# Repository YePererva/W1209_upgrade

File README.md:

# W1209 modification

**Repository is work in progress**

This repository contains my vision of modification of widely used W1209 thermostat.
Here, I want to introduce following changes:
- add "universal" schematic to use with either:
  - 10-20K NTC (as original W1209)
  - DS18B20
  - TMP36 and alike
  - LMx35 and alike
- add a capacitor for RESET line of to prevent self-restart\
  as reported here: [1](https://sampawno.ru/viewtopic.php?f=120&t=13251)
- Replace some custom sized SRA-12VDC-AL relay with more generiac. Like OMRON or something

# Remarks
- These thermostats were designed with [STM8S103F3P6](https://www.st.com/resource/en/datasheet/stm8s103f2.pdf) microcontrollers, but there are variations with [Nuvoton N76003AT20](https://direct.nuvoton.com/en/n76e003at20) MCU. The spare microcontroller can be salvaged from cheap STM8S103F3P6 devboards \
  (examples [1](https://vivonomicon.com/2018/07/15/the-w1209-a-sometimes-stm8-based-digital-thermostat/), [2](https://www.youtube.com/watch?v=e2FIBK9F2Js)).

# References
- The schematic of original module is "reviewed" here: \
  [1](https://chinese-electronics-products-tested.blogspot.com/p/w1209-temperature-controller-tested.html),
  [2](http://www.mastervintik.ru/obzor-tsifrovogo-modulya-termoregulyatora-w1209/),
  [3](https://tenbaht.github.io/sduino/hardware/w1209-thermostat/)

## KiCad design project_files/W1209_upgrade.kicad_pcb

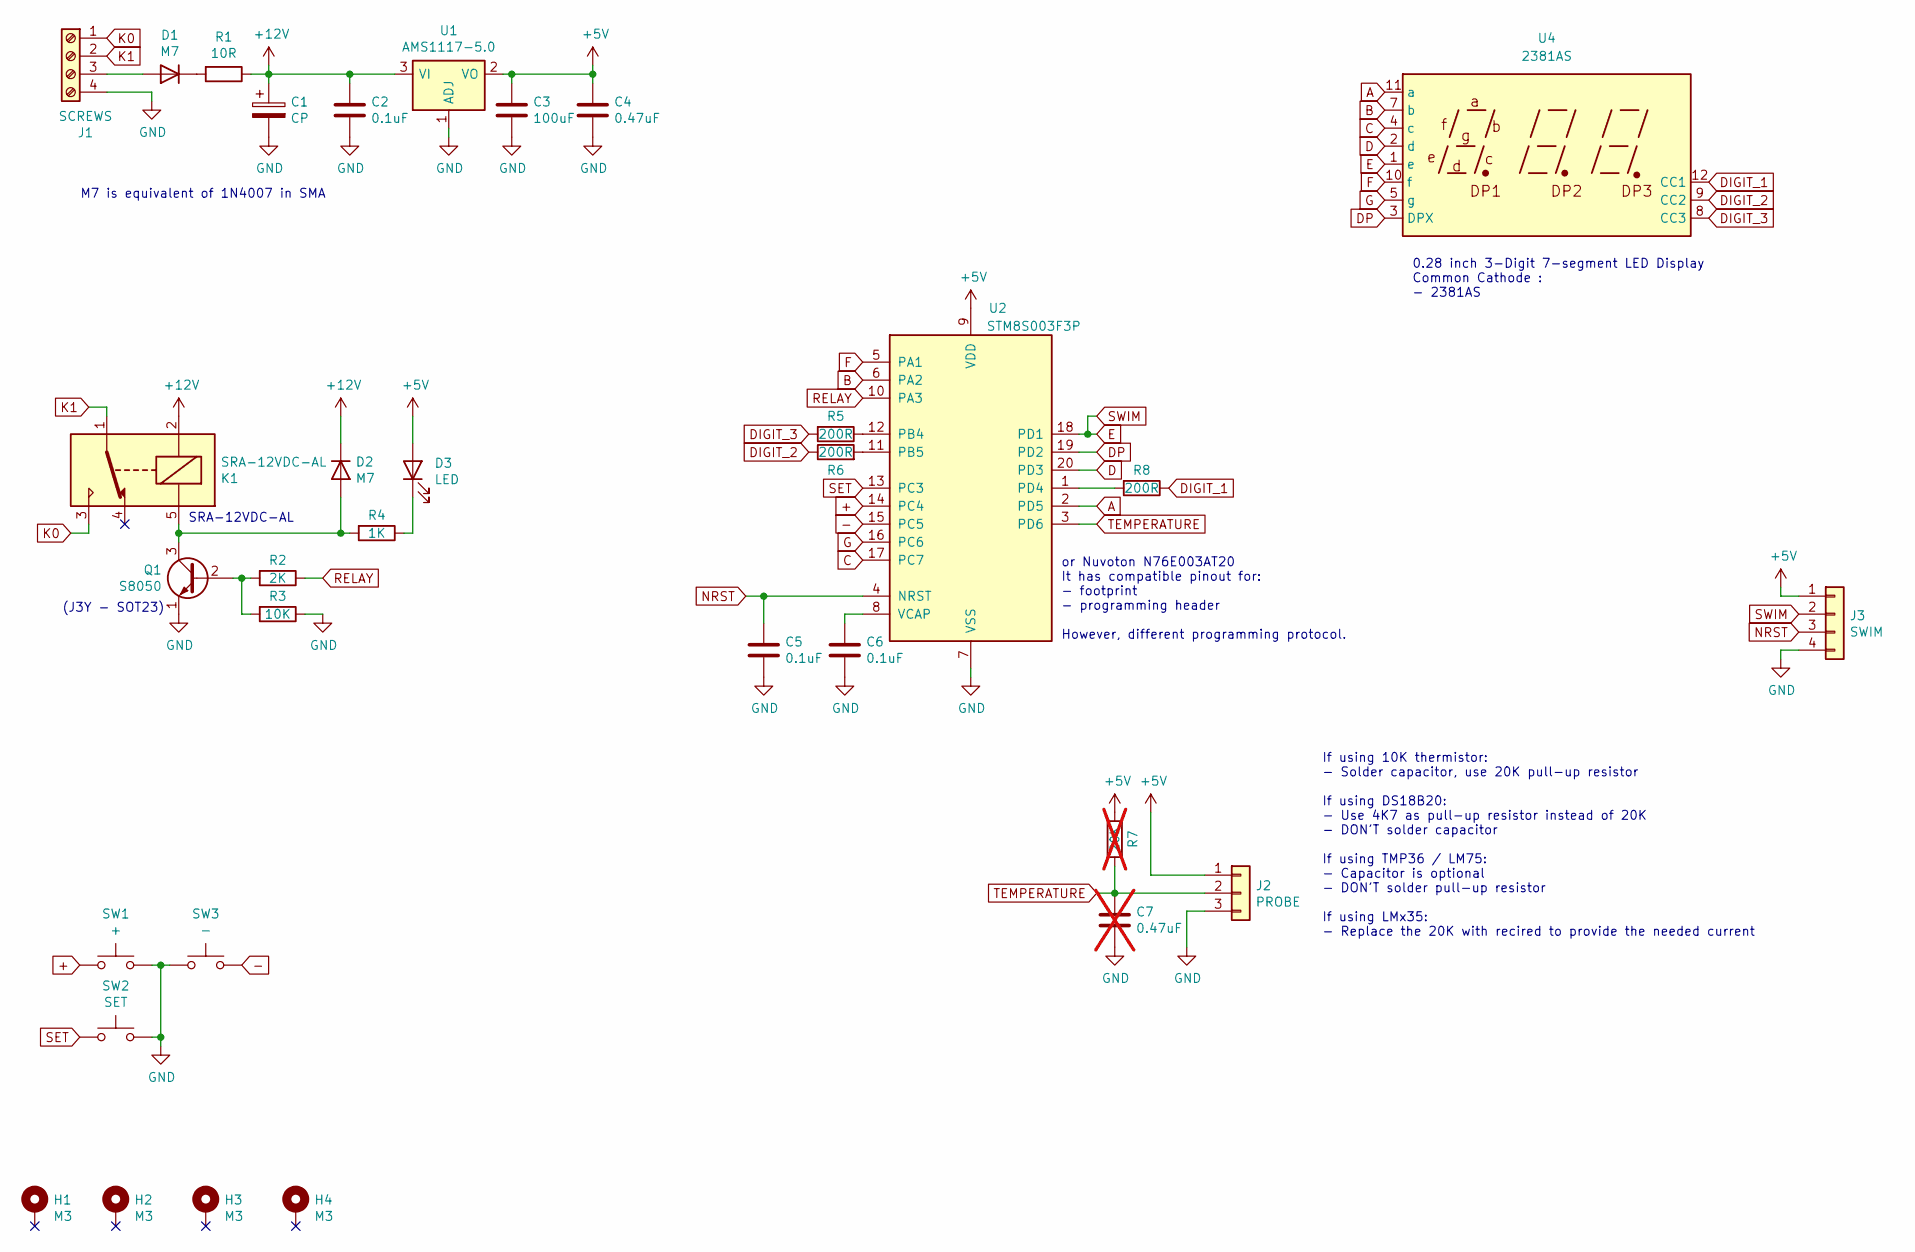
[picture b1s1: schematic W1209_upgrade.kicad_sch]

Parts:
C1: CP; CP_EIA-3528-12_Kemet-T_HandSolder
C2, C5, C6: 0.1uF; C_0805_2012Metric
C3: 100uF; C_0805_2012Metric
C4: 0.47uF; C_0805_2012Metric
C7: 0.47uF; C_0805_2012Metric; not fitted
D1, D2: M7; D_SMA
D3: LED; LED_0805_2012Metric
H1, H2, H3, H4: M3; MountingHole_3.2mm_M3_ISO14580_Pad
J1: SCREWS; TerminalBlock_Phoenix_PT-1,5-4-3.5-H_1x04_P3.50mm_Horizontal
J2: PROBE; PinHeader_1x03_P2.54mm_Vertical
J3: SWIM; PinHeader_1x04_P2.54mm_Vertical
K1: SRA-12VDC-AL; SRA
Q1: S8050; SOT-23
R1: 10R; R_0805_2012Metric
R2: 2K; R_0805_2012Metric
R3: 10K; R_0805_2012Metric
R4: 1K; R_0805_2012Metric
R5, R6, R8: 200R; R_0805_2012Metric
R7: 20K; R_0805_2012Metric; not fitted
SW1: +; SW_PUSH_6mm
SW2: SET; SW_PUSH_6mm
SW3: -; SW_PUSH_6mm
U1: AMS1117-5.0; SOT-223-3_TabPin2
U2: STM8S003F3P; TSSOP-20_4.4x6.5mm_P0.65mm
U4: 2381AS; 2381

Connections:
+: SW1.1, U2.14 (PC4)
+5V: C3.1, C4.1, D3.2 (A), J2.1, J3.1, R7.1, U1.2 (VO), U2.9 (VDD)
+12V: C1.1, C2.1, D2.1 (K), K1.2, R1.1, U1.3 (VI)
-: SW3.1, U2.15 (PC5)
A: U2.2 (PD5), U4.11 (a)
B: U2.6 (PA2), U4.7 (b)
C: U2.17 (PC7), U4.4 (c)
D: U2.20 (PD3), U4.2 (d)
DIGIT_1: R8.1, U4.12 (CC1)
DIGIT_2: R6.1, U4.9 (CC2)
DIGIT_3: R5.2, U4.8 (CC3)
DP: U2.19 (PD2), U4.3 (DPX)
E: J3.2, U2.18 (PD1), U4.1 (e)
F: U2.5 (PA1), U4.10 (f)
G: U2.16 (PC6), U4.5 (g)
GND: C1.2, C2.2, C3.2, C4.2, C5.2, C6.2, C7.2, J1.4, J2.3, J3.4, Q1.1 (E), R3.1, SW1.2, SW2.2, SW3.2, U1.1 (ADJ), U2.7 (VSS)
K0: J1.1, K1.3
K1: J1.2, K1.1
NRST: C5.1, J3.3, U2.4 (NRST)
unnamed: D1.2 (A), J1.3
unnamed: D1.1 (K), R1.2
unnamed: D2.2 (A), K1.5, Q1.3 (C), R4.2
unnamed: D3.1 (K), R4.1
unnamed: Q1.2 (B), R2.2, R3.2
unnamed: R5.1, U2.12 (PB4)
unnamed: R6.2, U2.11 (PB5)
unnamed: R8.2, U2.1 (PD4)
unnamed: C6.1, U2.8 (VCAP)
RELAY: R2.1, U2.10 (PA3)
SET: SW2.1, U2.13 (PC3)
TEMPERATURE: C7.1, J2.2, R7.2, U2.3 (PD6)

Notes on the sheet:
If using 10K thermistor: - Solder capacitor, use 20K pull-up resistor If using DS18B20: - Use 4K7 as pull-up resistor instead of 20K - DON'T solder capacitor If using TMP36 / LM75: - Capacitor is optional - DON'T solder pull-up resistor If using LMx35: - Replace the 20K with recired to provide the 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
or Nuvoton N76E003AT20 It has compatible pinout for: - footprint - programming header However, different programming protocol.
M7 is equivalent of 1N4007 in SMA
0.28 inch 3-Digit 7-segment LED Display Common Cathode : - 2381AS
(J3Y - SOT23)
SRA-12VDC-AL

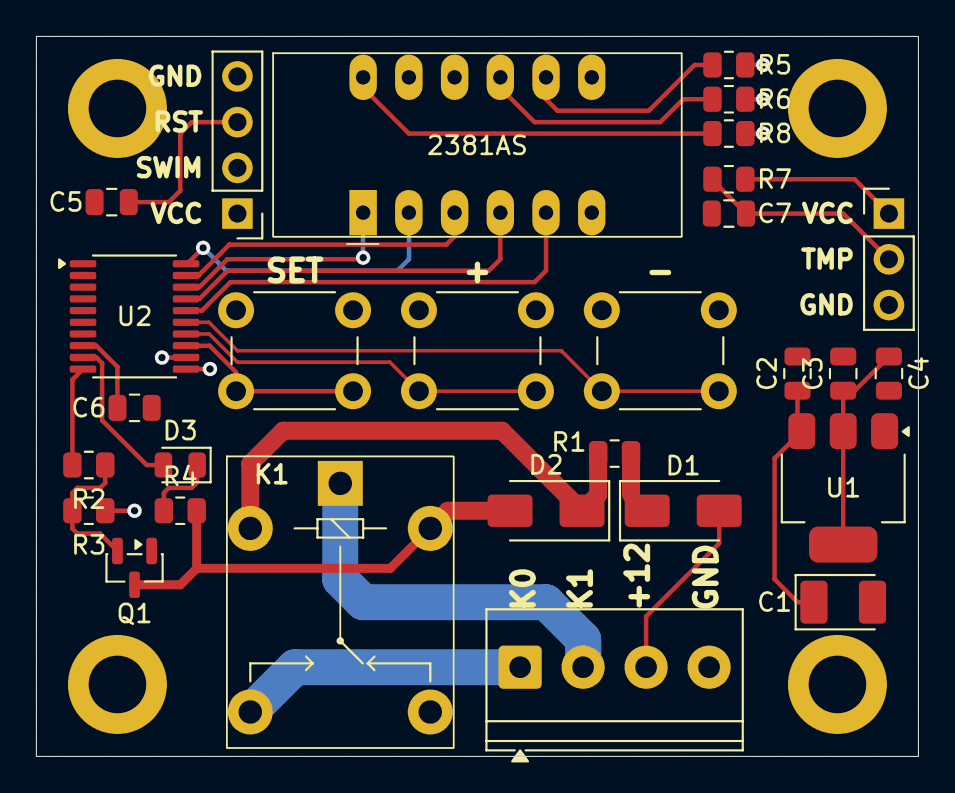
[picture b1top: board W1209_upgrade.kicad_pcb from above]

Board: 2 copper layers, 49.0 x 40.0 mm, 33 parts (0 on the bottom side), 31 nets.

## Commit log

2021-02-03 refresh
2021-05-05 added some references
2021-06-16 Comments correction
2025-04-12 Reopened in the recent kicad
2025-04-12 added a few datasheets
2026-04-02 updated to KiCAD 10
2026-04-14 layout
2026-06-24 COnverted to KiCAD 10.0.4
